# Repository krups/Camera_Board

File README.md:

# Camera_Board
Eagle files for the Camera Board on KREM

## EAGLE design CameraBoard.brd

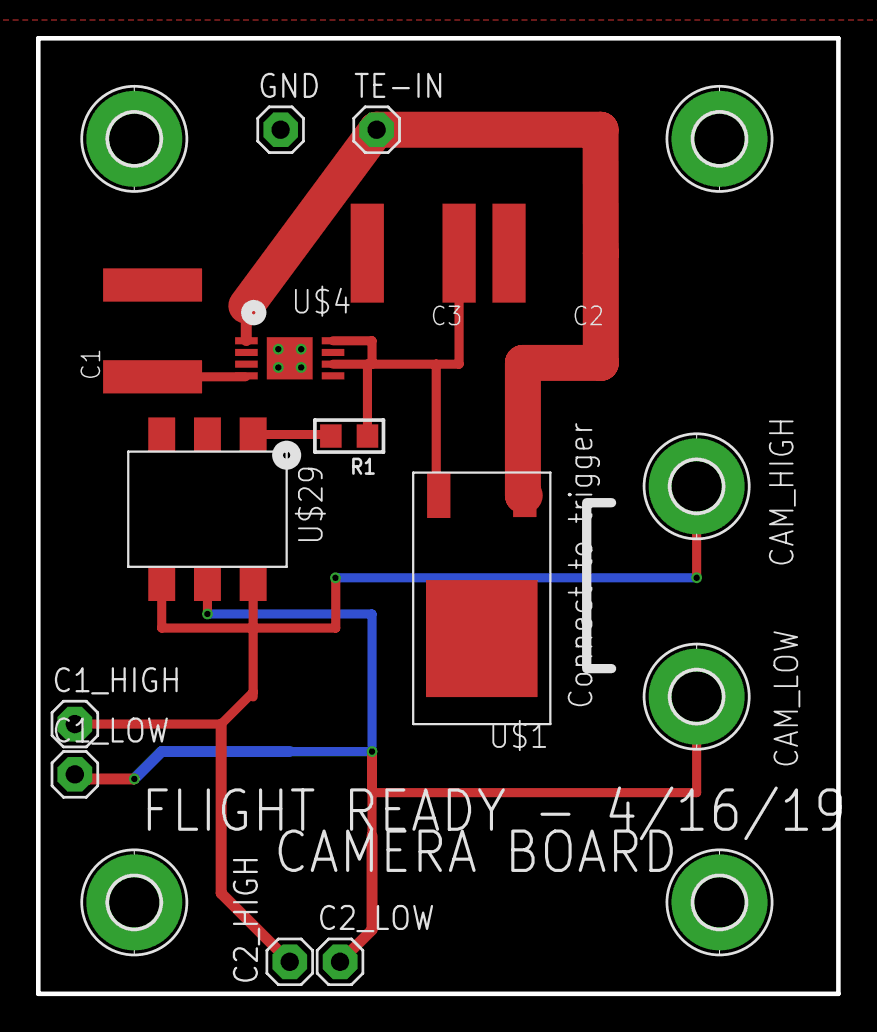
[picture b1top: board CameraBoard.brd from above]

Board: 2 copper layers, 44.5 x 53.1 mm, 19 parts (0 on the bottom side), 7 nets.

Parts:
C1: 0.1uF; C2220K
C1_HIGH, C1_LOW, C2_HIGH, C2_LOW: 1X01
C2: 1uF; C2220K
C3: 10uF; C2220K
GND: 1X01
H1, H2, H3, H4, H5, H6: MOUNT-PAD-ROUND2.8; 2,8-PAD
R1: 288; _0805
TE-IN: 1X01
U$1: C3D06065E; TO-252
U$4: MIC5282-5.0YMME; MSOP8-EPAD
U$29: AQV252GA; DIP6

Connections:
CAM_HIGH: C1_HIGH.1, C2_HIGH.1, H5.B2,8, U$29.4, U$29.6
CAM_LOW: C1_LOW.1, C2_LOW.1, H6.B2,8, U$29.5
GND: C1.2, C2.2, C3.2, GND.1, H1.B2,8, H2.B2,8, H3.B2,8, H4.B2,8, U$4.P$5, U$4.P$9, U$4.P$10, U$4.P$11, U$4.P$12, U$4.P$13, U$29.2
unnamed: C1.1, U$4.P$4
unnamed: R1.2, U$29.1
TE-IN: C2.1, TE-IN.1, U$1.P$1, U$4.P$1
V_REG: C3.1, R1.1, U$1.P$2, U$4.P$6, U$4.P$8

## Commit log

2019-05-16 Init commit, status as of balloon flight
2019-05-16 Removed JSTs, updated revision

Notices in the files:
parts and their libraries:
microbuilder: This work is placed in the public domain, and may be freely used for commercial and non-commercial work with the following conditions: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
